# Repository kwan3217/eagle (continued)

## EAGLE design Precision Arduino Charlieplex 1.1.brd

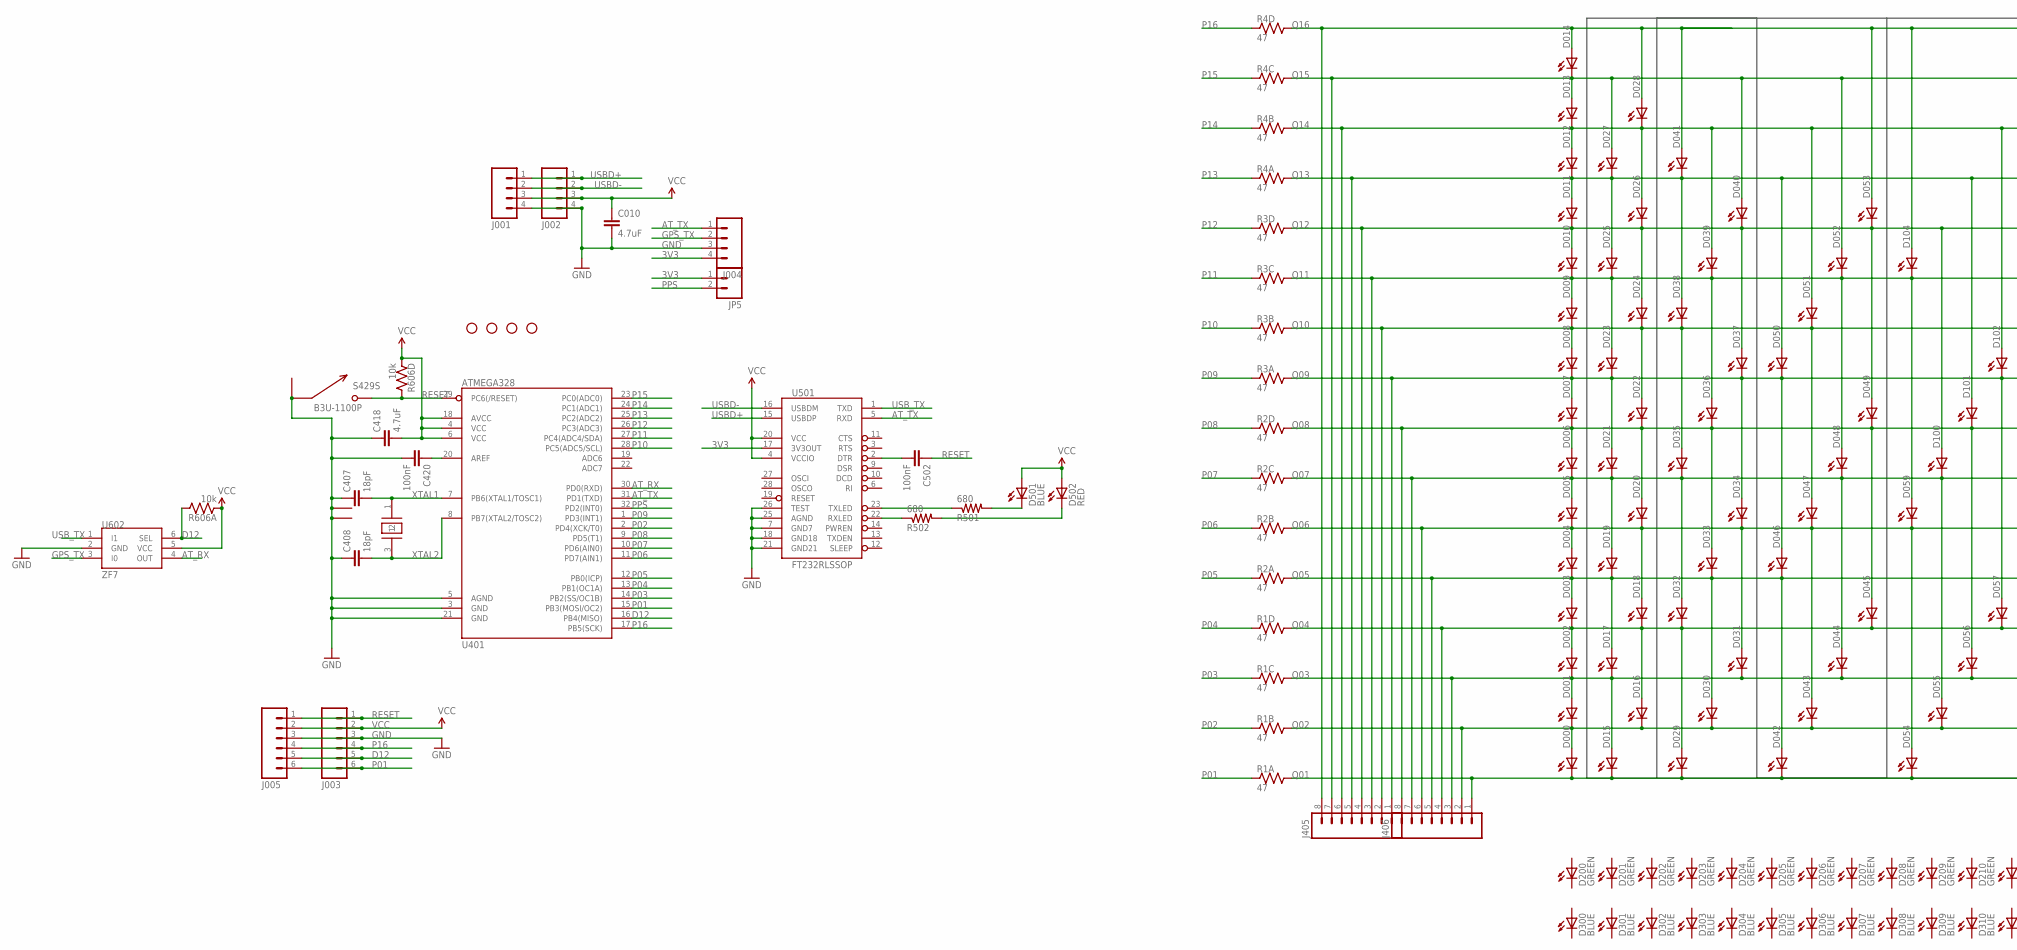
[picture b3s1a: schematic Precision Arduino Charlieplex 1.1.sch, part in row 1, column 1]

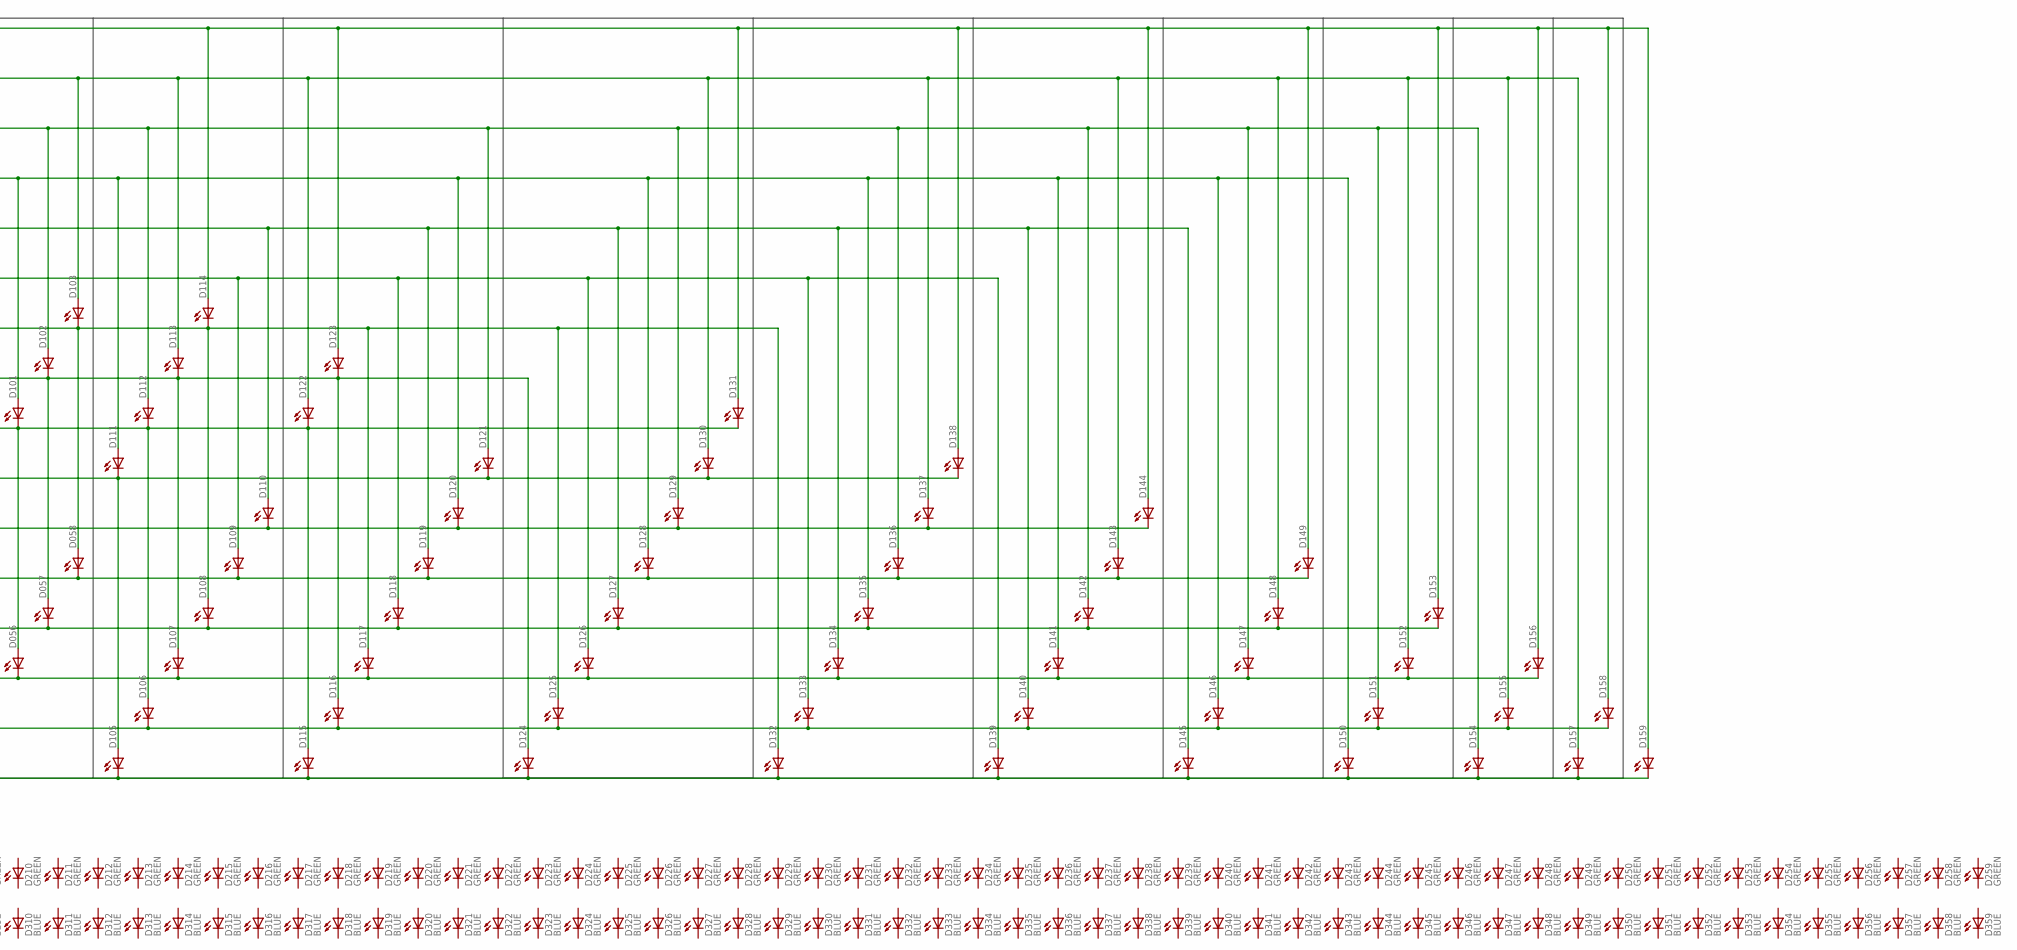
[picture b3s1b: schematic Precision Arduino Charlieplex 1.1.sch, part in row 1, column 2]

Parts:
C010, C418: 4.7uF; 0603-CAP; DIGIKEY 445-7483-1-ND
C407, C408: 18pF; 0603-CAP; DIGIKEY 478-6025-1-ND
C420, C502: 100nF; 0603-CAP; DIGIKEY 445-1316-1-ND
D000, D001, D002, D003, D004, D005, D006, D007, D008, D009, D010, D011, D012, D013, D014, D015, D016, D017, D018, D019, D020, D021, D022, D023, D024, D025, D026, D027, D028, D029, D030, D031, D032, D033, D034, D035, D036, D037, D038, D039, D040, D041, D042, D043, D044, D045, D046, D047, D048, D049, D050, D051, D052, D053, D054, D055, D056, D057, D058, D059, D502: RED; LED-0603; DIGIKEY 754-1359-1-ND
D100, D101, D102, D103, D104, D105, D106, D107, D108, D109, D110, D111, D112, D113, D114, D115, D116, D117, D118, D119, D120, D121, D122, D123, D124, D125, D126, D127, D128, D129, D130, D131, D132, D133, D134, D135, D136, D137, D138, D139, D140, D141, D142, D143, D144, D145, D146, D147, D148, D149, D150, D151, D152, D153, D154, D155, D156, D157, D158, D159: YELLOW; LED-0603; DIGIKEY 754-1124-1-ND
D200, D201, D202, D203, D204, D205, D206, D207, D208, D209, D210, D211, D212, D213, D214, D215, D216, D217, D218, D219, D220, D221, D222, D223, D224, D225, D226, D227, D228, D229, D230, D231, D232, D233, D234, D235, D236, D237, D238, D239, D240, D241, D242, D243, D244, D245, D246, D247, D248, D249, D250, D251, D252, D253, D254, D255, D256, D257, D258, D259: GREEN; LED-0603; DIGIKEY 350-2036-1-ND
D300, D301, D302, D303, D304, D305, D306, D307, D308, D309, D310, D311, D312, D313, D314, D315, D316, D317, D318, D319, D320, D321, D322, D323, D324, D325, D326, D327, D328, D329, D330, D331, D332, D333, D334, D335, D336, D337, D338, D339, D340, D341, D342, D343, D344, D345, D346, D347, D348, D349, D350, D351, D352, D353, D354, D355, D356, D357, D358, D359, D501: BLUE; LED-0603; DIGIKEY 350-2037-1-ND
J001, J002, J004: M04PTH; 1X04; DIGIKEY $NOPART
J003, J005: M06SIP; 1X06; DIGIKEY $NOPART
J405, J406: M081X08; 1X08; DIGIKEY $NOPART
JP1, JP2, JP3, JP4: STAND-OFF; DIGIKEY $NOPART
JP5: M02PTH; 1X02; DIGIKEY $NOPART
R1, R2, R3, R4: 47; CRA04; DIGIKEY CRA4S847CT-ND
R501, R502: 680; 0603-RES; DIGIKEY P680GCT-ND
R606: 10k; CRA04; DIGIKEY CRA4S810KCT-ND
S429: B3U-1100P; DIGIKEY SW1021CT-ND
U401: ATMEGA328; TQFP32-08; DIGIKEY ATMEGA328P-15AZCT-ND
U501: FT232RLSSOP; SSOP28DB; DIGIKEY 768-1007-1-ND
U602: ZF7; SC-70-6; DIGIKEY NC7SZ157P6XCT-ND
Y401: 16MHz; CRYSTAL_SMD; DIGIKEY 887-1319-1-ND

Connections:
3V3: J004.4, JP5.1, U501.17 (3V3OUT)
AREF: C420.1, U401.20 (AREF)
AT_RX: U401.30 (PD0(RXD)), U602.4 (OUT)
AT_TX: J004.1, U401.31 (PD1(TXD)), U501.5 (RXD)
D12: J003.5, J005.5, R606.8 (2), U401.16 (PB4(MISO)), U602.6 (SEL)
GND: C010.2, C407.1, C408.1, C418.1, C420.2, J001.4, J002.4, J003.3, J004.3, J005.3, S429.P$1 (1), S429.P$3 (1), U401.3 (GND), U401.5 (AGND), U401.21 (GND), U501.7 (GND7), U501.18 (GND18), U501.21 (GND21), U501.25 (AGND), U501.26 (TEST), U602.2 (GND), Y401.2 (1), Y401.4 (1)
GPS_TX: J004.2, U602.3 (I0)
unnamed: C502.2, U501.2 (DTR)
unnamed: D501.C, R501.2
unnamed: R501.1, U501.23 (TXLED)
unnamed: R502.1, U501.22 (RXLED)
unnamed: D502.C, R502.2
P01: J003.6, J005.6, R1.1, U401.15 (PB3(MOSI/OC2))
P02: R1.2 (1), U401.2 (PD4(XCK/T0))
P03: R1.3 (1), U401.14 (PB2(SS/OC1B))
P04: R1.4 (1), U401.13 (PB1(OC1A))
P05: R2.1, U401.12 (PB0(ICP))
P06: R2.2 (1), U401.11 (PD7(AIN1))
P07: R2.3 (1), U401.10 (PD6(AIN0))
P08: R2.4 (1), U401.9 (PD5(T1))
P09: R3.1, U401.1 (PD3(INT1))
P10: R3.2 (1), U401.28 (PC5(ADC5/SCL))
P11: R3.3 (1), U401.27 (PC4(ADC4/SDA))
P12: R3.4 (1), U401.26 (PC3(ADC3))
P13: R4.1, U401.25 (PC2(ADC2))
P14: R4.2 (1), U401.24 (PC1(ADC1))
P15: R4.3 (1), U401.23 (PC0(ADC0))
P16: J003.4, J005.4, R4.4 (1), U401.17 (PB5(SCK))
PPS: JP5.2, U401.32 (PD2(INT0))
Q01: D000.C, D015.C, D029.C, D042.C, D054.C, D105.C, D115.C, D124.C, D132.C, D139.C, D145.C, D150.C, D154.C, D157.C, D159.C, J406.1, R1.8 (2)
Q02: D000.A, D001.C, D016.C, D030.C, D043.C, D055.C, D106.C, D116.C, D125.C, D133.C, D140.C, D146.C, D151.C, D155.C, D158.C, J406.2, R1.7 (2)
Q03: D001.A, D002.C, D015.A, D017.C, D031.C, D044.C, D056.C, D107.C, D117.C, D126.C, D134.C, D141.C, D147.C, D152.C, D156.C, J406.3, R1.6 (2)
Q04: D002.A, D003.C, D016.A, D018.C, D029.A, D032.C, D045.C, D057.C, D108.C, D118.C, D127.C, D135.C, D142.C, D148.C, D153.C, J406.4, R1.5 (2)
Q05: D003.A, D004.C, D017.A, D019.C, D030.A, D033.C, D042.A, D046.C, D058.C, D109.C, D119.C, D128.C, D136.C, D143.C, D149.C, J406.5, R2.8 (2)
Q06: D004.A, D005.C, D018.A, D020.C, D031.A, D034.C, D043.A, D047.C, D054.A, D059.C, D110.C, D120.C, D129.C, D137.C, D144.C, J406.6, R2.7 (2)
Q07: D005.A, D006.C, D019.A, D021.C, D032.A, D035.C, D044.A, D048.C, D055.A, D100.C, D105.A, D111.C, D121.C, D130.C, D138.C, J406.7, R2.6 (2)
Q08: D006.A, D007.C, D020.A, D022.C, D033.A, D036.C, D045.A, D049.C, D056.A, D101.C, D106.A, D112.C, D115.A, D122.C, D131.C, J406.8, R2.5 (2)
Q09: D007.A, D008.C, D021.A, D023.C, D034.A, D037.C, D046.A, D050.C, D057.A, D102.C, D107.A, D113.C, D116.A, D123.C, D124.A, J405.1, R3.8 (2)
Q10: D008.A, D009.C, D022.A, D024.C, D035.A, D038.C, D047.A, D051.C, D058.A, D103.C, D108.A, D114.C, D117.A, D125.A, D132.A, J405.2, R3.7 (2)
Q11: D009.A, D010.C, D023.A, D025.C, D036.A, D039.C, D048.A, D052.C, D059.A, D104.C, D109.A, D118.A, D126.A, D133.A, D139.A, J405.3, R3.6 (2)
Q12: D010.A, D011.C, D024.A, D026.C, D037.A, D040.C, D049.A, D053.C, D100.A, D110.A, D119.A, D127.A, D134.A, D140.A, D145.A, J405.4, R3.5 (2)
Q13: D011.A, D012.C, D025.A, D027.C, D038.A, D041.C, D050.A, D101.A, D111.A, D120.A, D128.A, D135.A, D141.A, D146.A, D150.A, J405.5, R4.8 (2)
Q14: D012.A, D013.C, D026.A, D028.C, D039.A, D051.A, D102.A, D112.A, D121.A, D129.A, D136.A, D142.A, D147.A, D151.A, D154.A, J405.6, R4.7 (2)
Q15: D013.A, D014.C, D027.A, D040.A, D052.A, D103.A, D113.A, D122.A, D130.A, D137.A, D143.A, D148.A, D152.A, D155.A, D157.A, J405.7, R4.6 (2)
Q16: D014.A, D028.A, D041.A, D053.A, D104.A, D114.A, D123.A, D131.A, D138.A, D144.A, D149.A, D153.A, D156.A, D158.A, D159.A, J405.8, R4.5 (2)
RESET: C502.1, J003.1, J005.1, R606.5 (2), S429.P$2 (2), U401.29 (PC6(/RESET))
USBD+: J001.1, J002.1, U501.15 (USBDP)
USBD-: J001.2, J002.2, U501.16 (USBDM)
USB_TX: U501.1 (TXD), U602.1 (I1)
VCC: C010.1, C418.2, D501.A, D502.A, J001.3, J002.3, J003.2, J005.2, R606.1, R606.4 (1), U401.4 (VCC), U401.6 (VCC), U401.18 (AVCC), U501.4 (VCCIO), U501.20 (VCC), U602.5 (VCC)
XTAL1: C407.2, U401.7 (PB6(XTAL1/TOSC1)), Y401.1
XTAL2: C408.2, U401.8 (PB7(XTAL2/TOSC2)), Y401.3 (2)

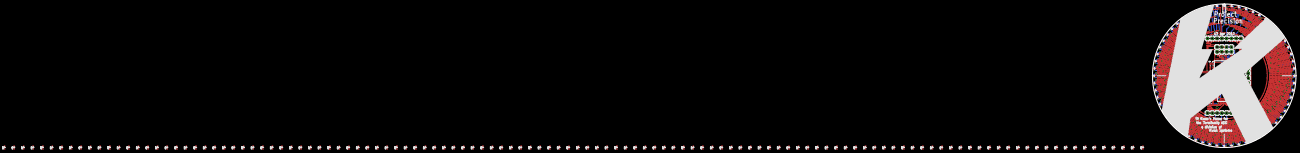
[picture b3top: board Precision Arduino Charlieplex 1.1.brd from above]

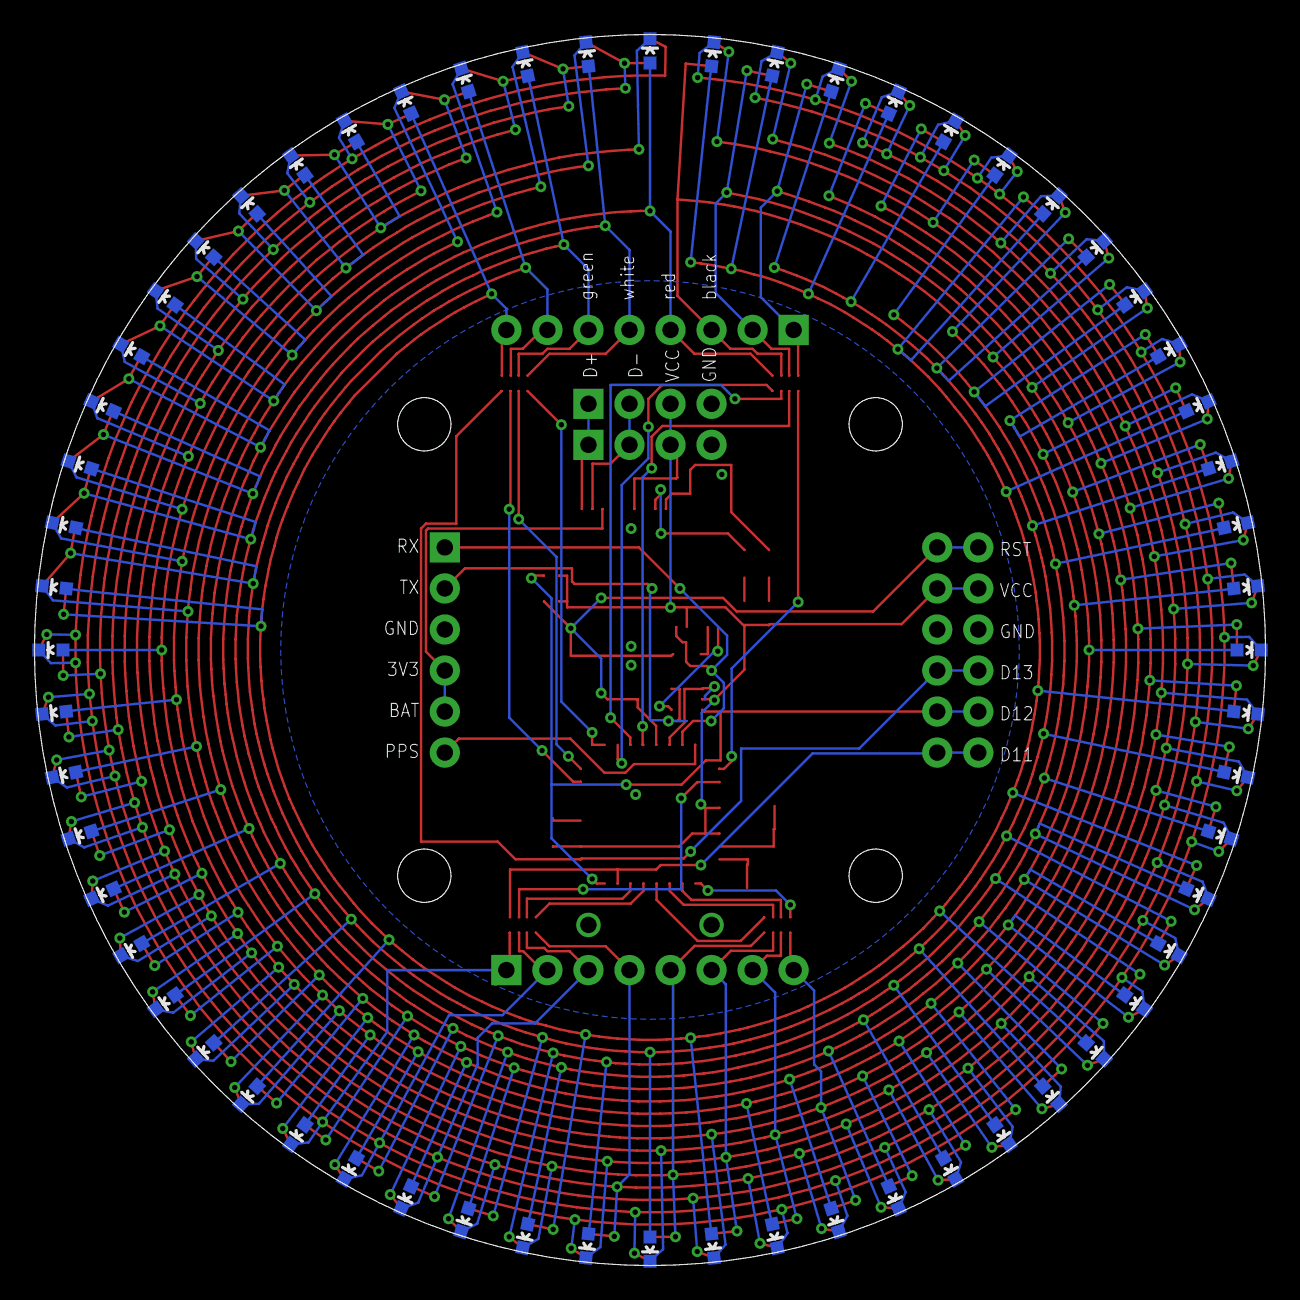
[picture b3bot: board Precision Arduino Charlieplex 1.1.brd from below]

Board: 2 copper layers, 76.2 x 76.2 mm, 272 parts (60 on the bottom side), 52 nets.

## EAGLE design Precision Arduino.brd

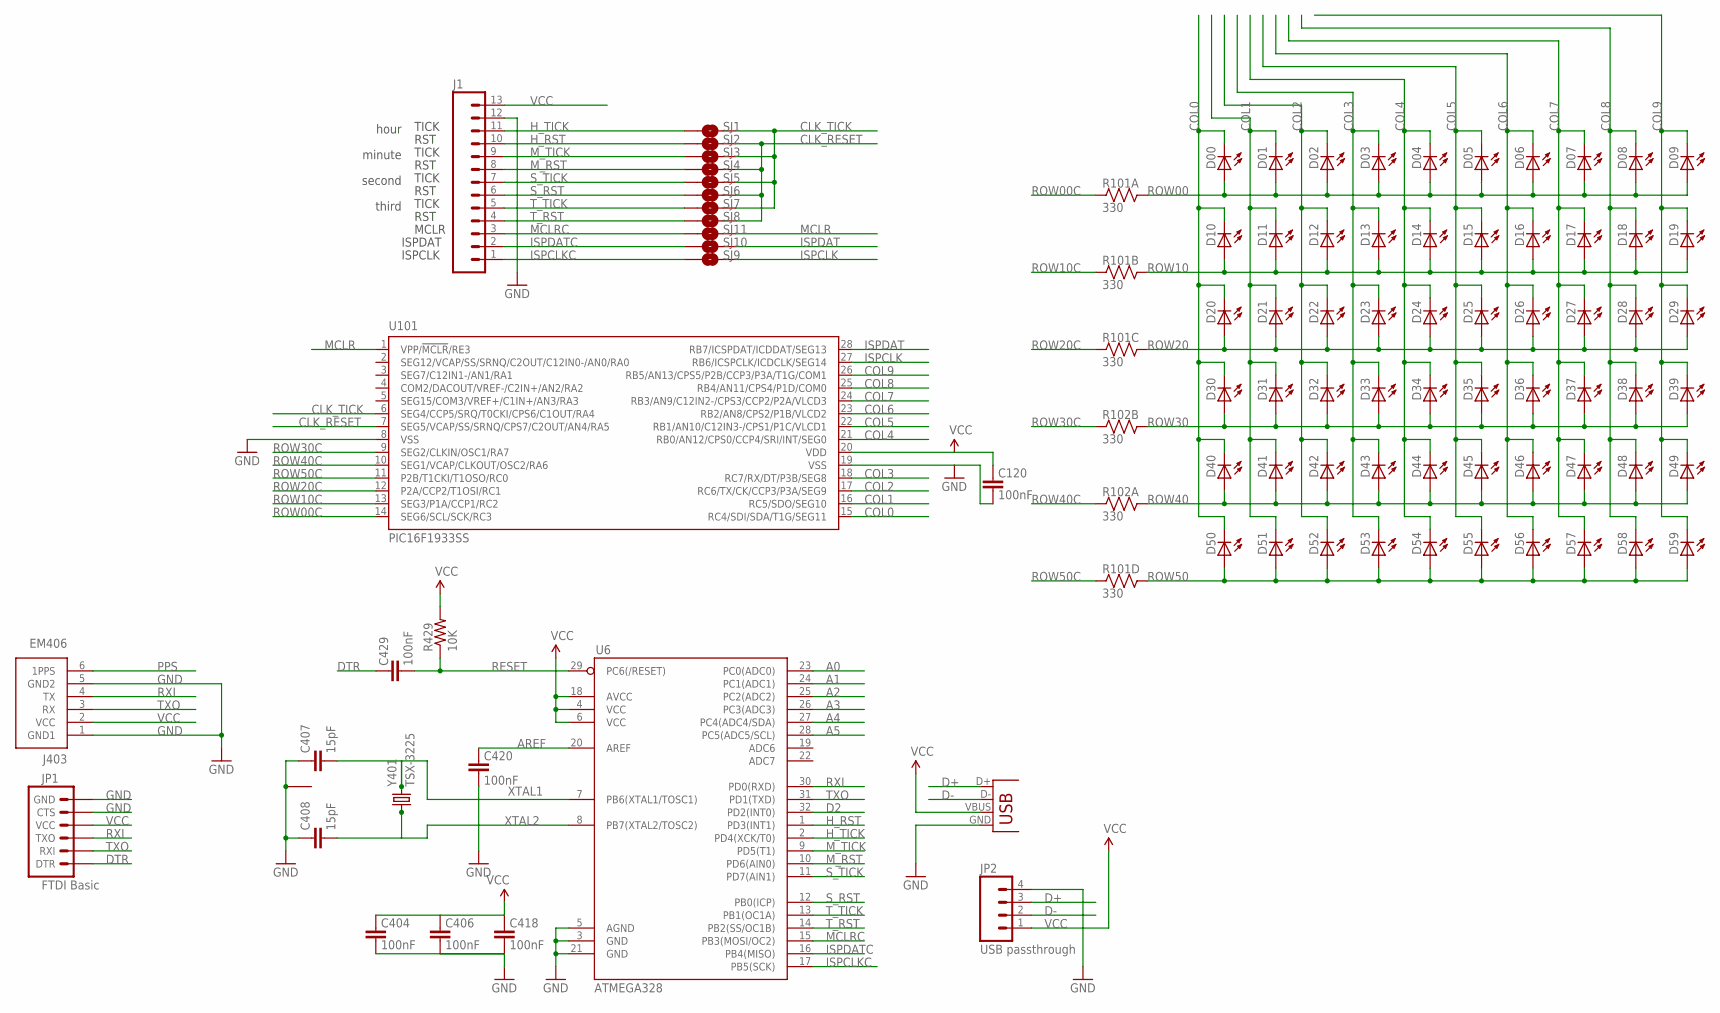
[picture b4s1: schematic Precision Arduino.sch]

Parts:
C120, C404, C406, C418, C420, C429: 100nF; 0402-CAP
C407, C408: 15pF; 0402-CAP
D00, D01, D02, D03, D04, D05, D06, D07, D08, D09, D10, D11, D12, D13, D14, D15, D16, D17, D18, D19, D20, D21, D22, D23, D24, D25, D26, D27, D28, D29, D30, D31, D32, D33, D34, D35, D36, D37, D38, D39, D40, D41, D42, D43, D44, D45, D46, D47, D48, D49, D50, D51, D52, D53, D54, D55, D56, D57, D58, D59: LED3MM
J1: M13; 1X13
J403: EM406
JP1: FTDI Basic; 1X06
JP2: USB passthrough; 1X04
R101, R102: 330; CRA06
R429: 10K; 0402-RES
SJ1, SJ2, SJ3, SJ4, SJ5, SJ6, SJ7, SJ8, SJ9, SJ10, SJ11: SOLDERJUMPERNO; SJ_2S-NO
U6: ATMEGA328; TQFP32-08
U101: PIC16F1933SS; SSOP28
X1: USB-MICROB
Y401: TSX-3225; CRYSTAL_SMD

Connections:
A0: U6.23 (PC0(ADC0))
A1: U6.24 (PC1(ADC1))
A2: U6.25 (PC2(ADC2))
A3: U6.26 (PC3(ADC3))
A4: U6.27 (PC4(ADC4/SDA))
A5: U6.28 (PC5(ADC5/SCL))
AREF: C420.2, U6.20 (AREF)
CLK_RESET: SJ2.2, SJ4.2, SJ6.2, SJ8.2, U101.7 (SEG5/VCAP/SS/SRNQ/CPS7/C2OUT/AN4/RA5)
CLK_TICK: SJ1.2, SJ3.2, SJ5.2, SJ7.2, U101.6 (SEG4/CCP5/SRQ/T0CKI/CPS6/C1OUT/RA4)
COL0: D00.K (C), D10.K (C), D20.K (C), D30.K (C), D40.K (C), D50.K (C), U101.15 (RC4/SDI/SDA/T1G/SEG11)
COL1: D01.K (C), D11.K (C), D21.K (C), D31.K (C), D41.K (C), D51.K (C), U101.16 (RC5/SDO/SEG10)
COL2: D02.K (C), D12.K (C), D22.K (C), D32.K (C), D42.K (C), D52.K (C), U101.17 (RC6/TX/CK/CCP3/P3A/SEG9)
COL3: D03.K (C), D13.K (C), D23.K (C), D33.K (C), D43.K (C), D53.K (C), U101.18 (RC7/RX/DT/P3B/SEG8)
COL4: D04.K (C), D14.K (C), D24.K (C), D34.K (C), D44.K (C), D54.K (C), U101.21 (RB0/AN12/CPS0/CCP4/SRI/INT/SEG0)
COL5: D05.K (C), D15.K (C), D25.K (C), D35.K (C), D45.K (C), D55.K (C), U101.22 (RB1/AN10/C12IN3-/CPS1/P1C/VLCD1)
COL6: D06.K (C), D16.K (C), D26.K (C), D36.K (C), D46.K (C), D56.K (C), U101.23 (RB2/AN8/CPS2/P1B/VLCD2)
COL7: D07.K (C), D17.K (C), D27.K (C), D37.K (C), D47.K (C), D57.K (C), U101.24 (RB3/AN9/C12IN2-/CPS3/CCP2/P2A/VLCD3)
COL8: D08.K (C), D18.K (C), D28.K (C), D38.K (C), D48.K (C), D58.K (C), U101.25 (RB4/AN11/CPS4/P1D/COM0)
COL9: D09.K (C), D19.K (C), D29.K (C), D39.K (C), D49.K (C), D59.K (C), U101.26 (RB5/AN13/CPS5/P2B/CCP3/P3A/T1G/COM1)
D2: U6.32 (PD2(INT0))
D+: JP2.3, X1.D+
D-: JP2.2, X1.D-
DTR: C429.2, JP1.1 (DTR)
GND: C120.1, C404.1, C406.1, C407.1, C408.1, C418.1, C420.1, J1.12, J403.1 (GND1), J403.5 (GND2), JP1.5 (CTS), JP1.6 (GND), JP2.4, U6.3 (GND), U6.5 (AGND), U6.21 (GND), U101.8 (VSS), U101.19 (VSS), X1.GND, Y401.2 (1), Y401.4 (1)
H_RST: J1.10, SJ2.1, U6.1 (PD3(INT1))
H_TICK: J1.11, SJ1.1, U6.2 (PD4(XCK/T0))
ISPCLK: SJ9.2, U101.27 (RB6/ICSPCLK/ICDCLK/SEG14)
ISPCLKC: J1.1, SJ9.1, U6.17 (PB5(SCK))
ISPDAT: SJ10.2, U101.28 (RB7/ICSPDAT/ICDDAT/SEG13)
ISPDATC: J1.2, SJ10.1, U6.16 (PB4(MISO))
MCLR: SJ11.2, U101.1 (VPP/!MCLR!/RE3)
MCLRC: J1.3, SJ11.1, U6.15 (PB3(MOSI/OC2))
M_RST: J1.8, SJ4.1, U6.10 (PD6(AIN0))
M_TICK: J1.9, SJ3.1, U6.9 (PD5(T1))
PPS: J403.6 (1PPS)
RESET: C429.1, R429.1, U6.29 (PC6(/RESET))
ROW00: D00.A, D01.A, D02.A, D03.A, D04.A, D05.A, D06.A, D07.A, D08.A, D09.A, R101.8 (2)
ROW00C: R101.1, U101.14 (SEG6/SCL/SCK/RC3)
ROW10: D10.A, D11.A, D12.A, D13.A, D14.A, D15.A, D16.A, D17.A, D18.A, D19.A, R101.7 (2)
ROW10C: R101.2 (1), U101.13 (SEG3/P1A/CCP1/RC2)
ROW20: D20.A, D21.A, D22.A, D23.A, D24.A, D25.A, D26.A, D27.A, D28.A, D29.A, R101.6 (2)
ROW20C: R101.3 (1), U101.12 (P2A/CCP2/T1OSI/RC1)
ROW30: D30.A, D31.A, D32.A, D33.A, D34.A, D35.A, D36.A, D37.A, D38.A, D39.A, R102.7 (2)
ROW30C: R102.2 (1), U101.9 (SEG2/CLKIN/OSC1/RA7)
ROW40: D40.A, D41.A, D42.A, D43.A, D44.A, D45.A, D46.A, D47.A, D48.A, D49.A, R102.8 (2)
ROW40C: R102.1, U101.10 (SEG1/VCAP/CLKOUT/OSC2/RA6)
ROW50: D50.A, D51.A, D52.A, D53.A, D54.A, D55.A, D56.A, D57.A, D58.A, D59.A, R101.5 (2)
ROW50C: R101.4 (1), U101.11 (P2B/T1CKI/T1OSO/RC0)
RXI: J403.4 (TX), JP1.3 (TXO), U6.30 (PD0(RXD))
S_RST: J1.6, SJ6.1, U6.12 (PB0(ICP))
S_TICK: J1.7, SJ5.1, U6.11 (PD7(AIN1))
TXO: J403.3 (RX), JP1.2 (RXI), U6.31 (PD1(TXD))
T_RST: J1.4, SJ8.1, U6.14 (PB2(SS/OC1B))
T_TICK: J1.5, SJ7.1, U6.13 (PB1(OC1A))
VCC: C120.2, C404.2, C406.2, C418.2, J1.13, J403.2 (VCC), JP1.4 (VCC), JP2.1, R429.2, U6.4 (VCC), U6.6 (VCC), U6.18 (AVCC), U101.20 (VDD), X1.VBUS
XTAL1: C407.2, U6.7 (PB6(XTAL1/TOSC1)), Y401.3 (2)
XTAL2: C408.2, U6.8 (PB7(XTAL2/TOSC2)), Y401.1

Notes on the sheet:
TICK
RST
hour
minute
second
third
MCLR
ISPCLK
ISPDAT

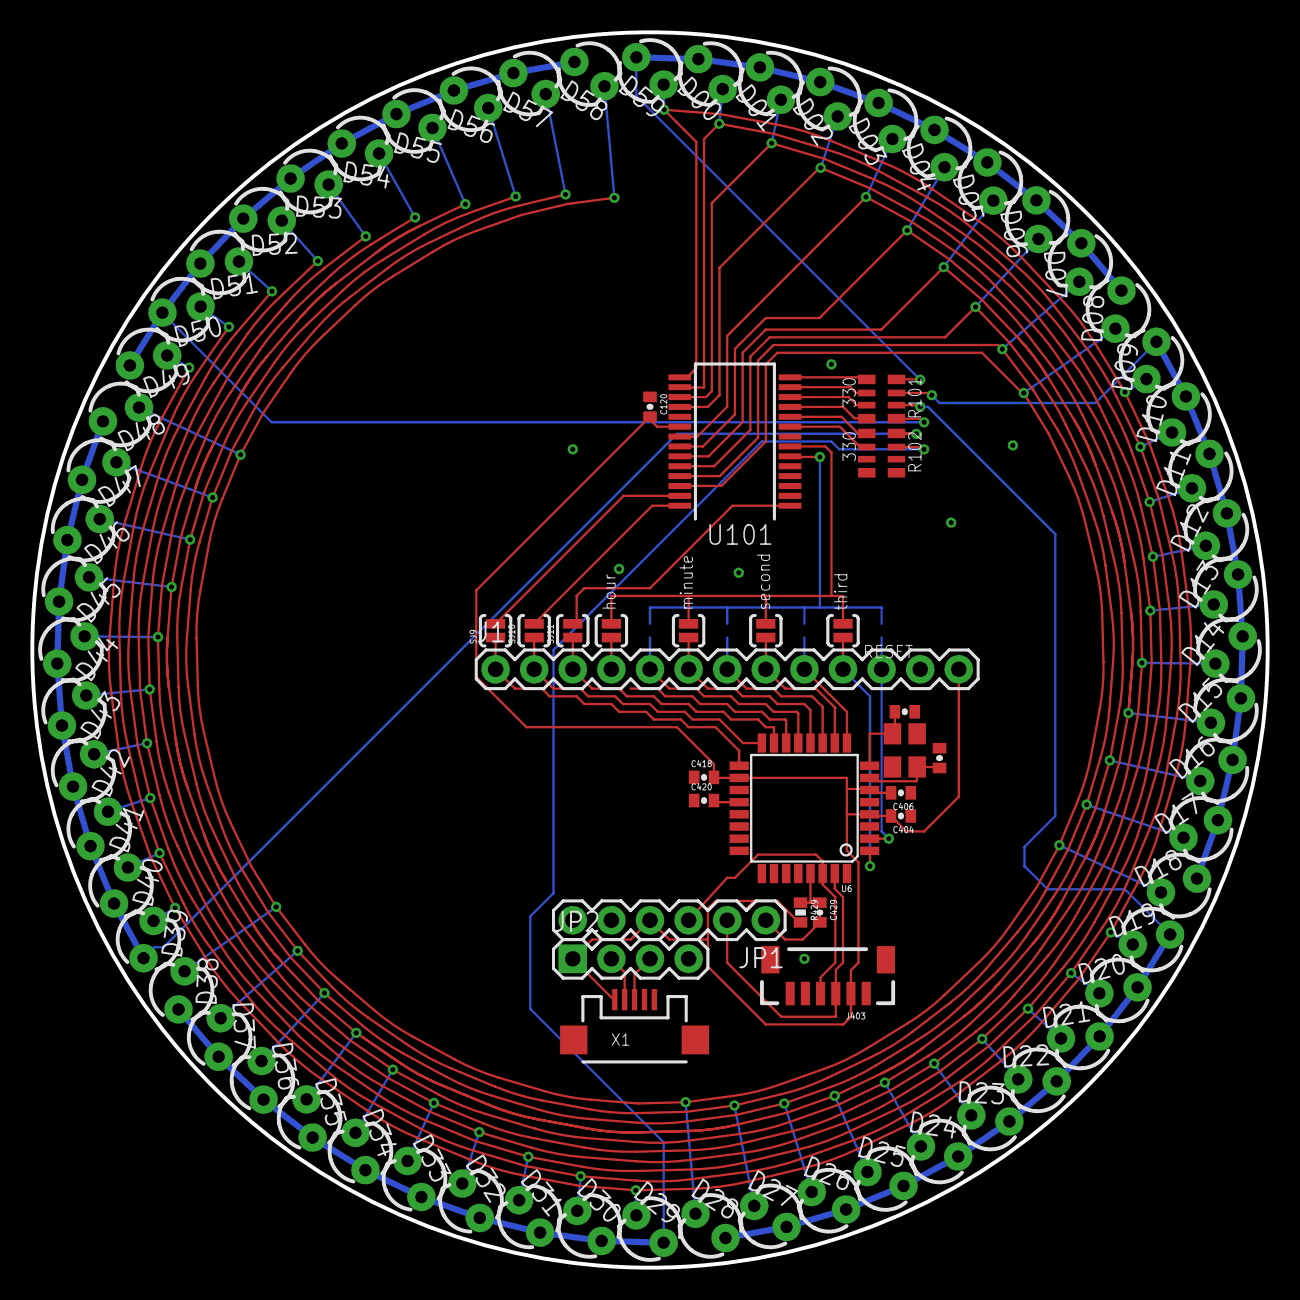
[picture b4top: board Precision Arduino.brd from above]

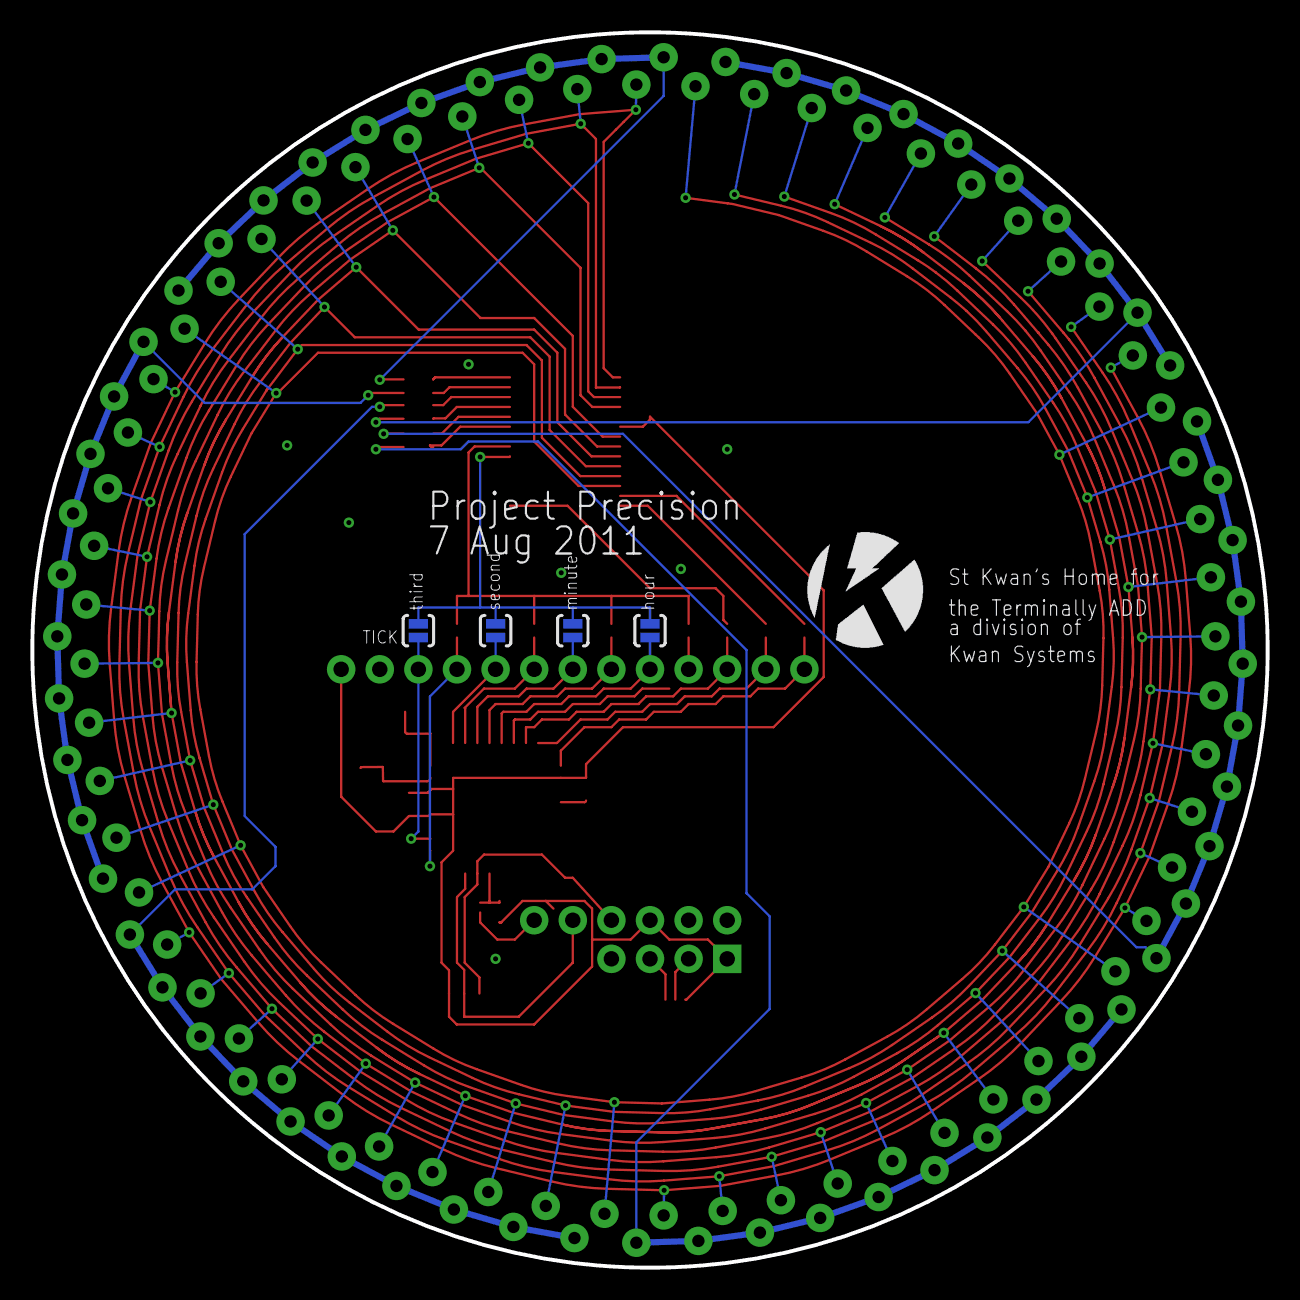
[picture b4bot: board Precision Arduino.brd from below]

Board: 2 copper layers, 81.3 x 81.3 mm, 90 parts (4 on the bottom side), 49 nets.
